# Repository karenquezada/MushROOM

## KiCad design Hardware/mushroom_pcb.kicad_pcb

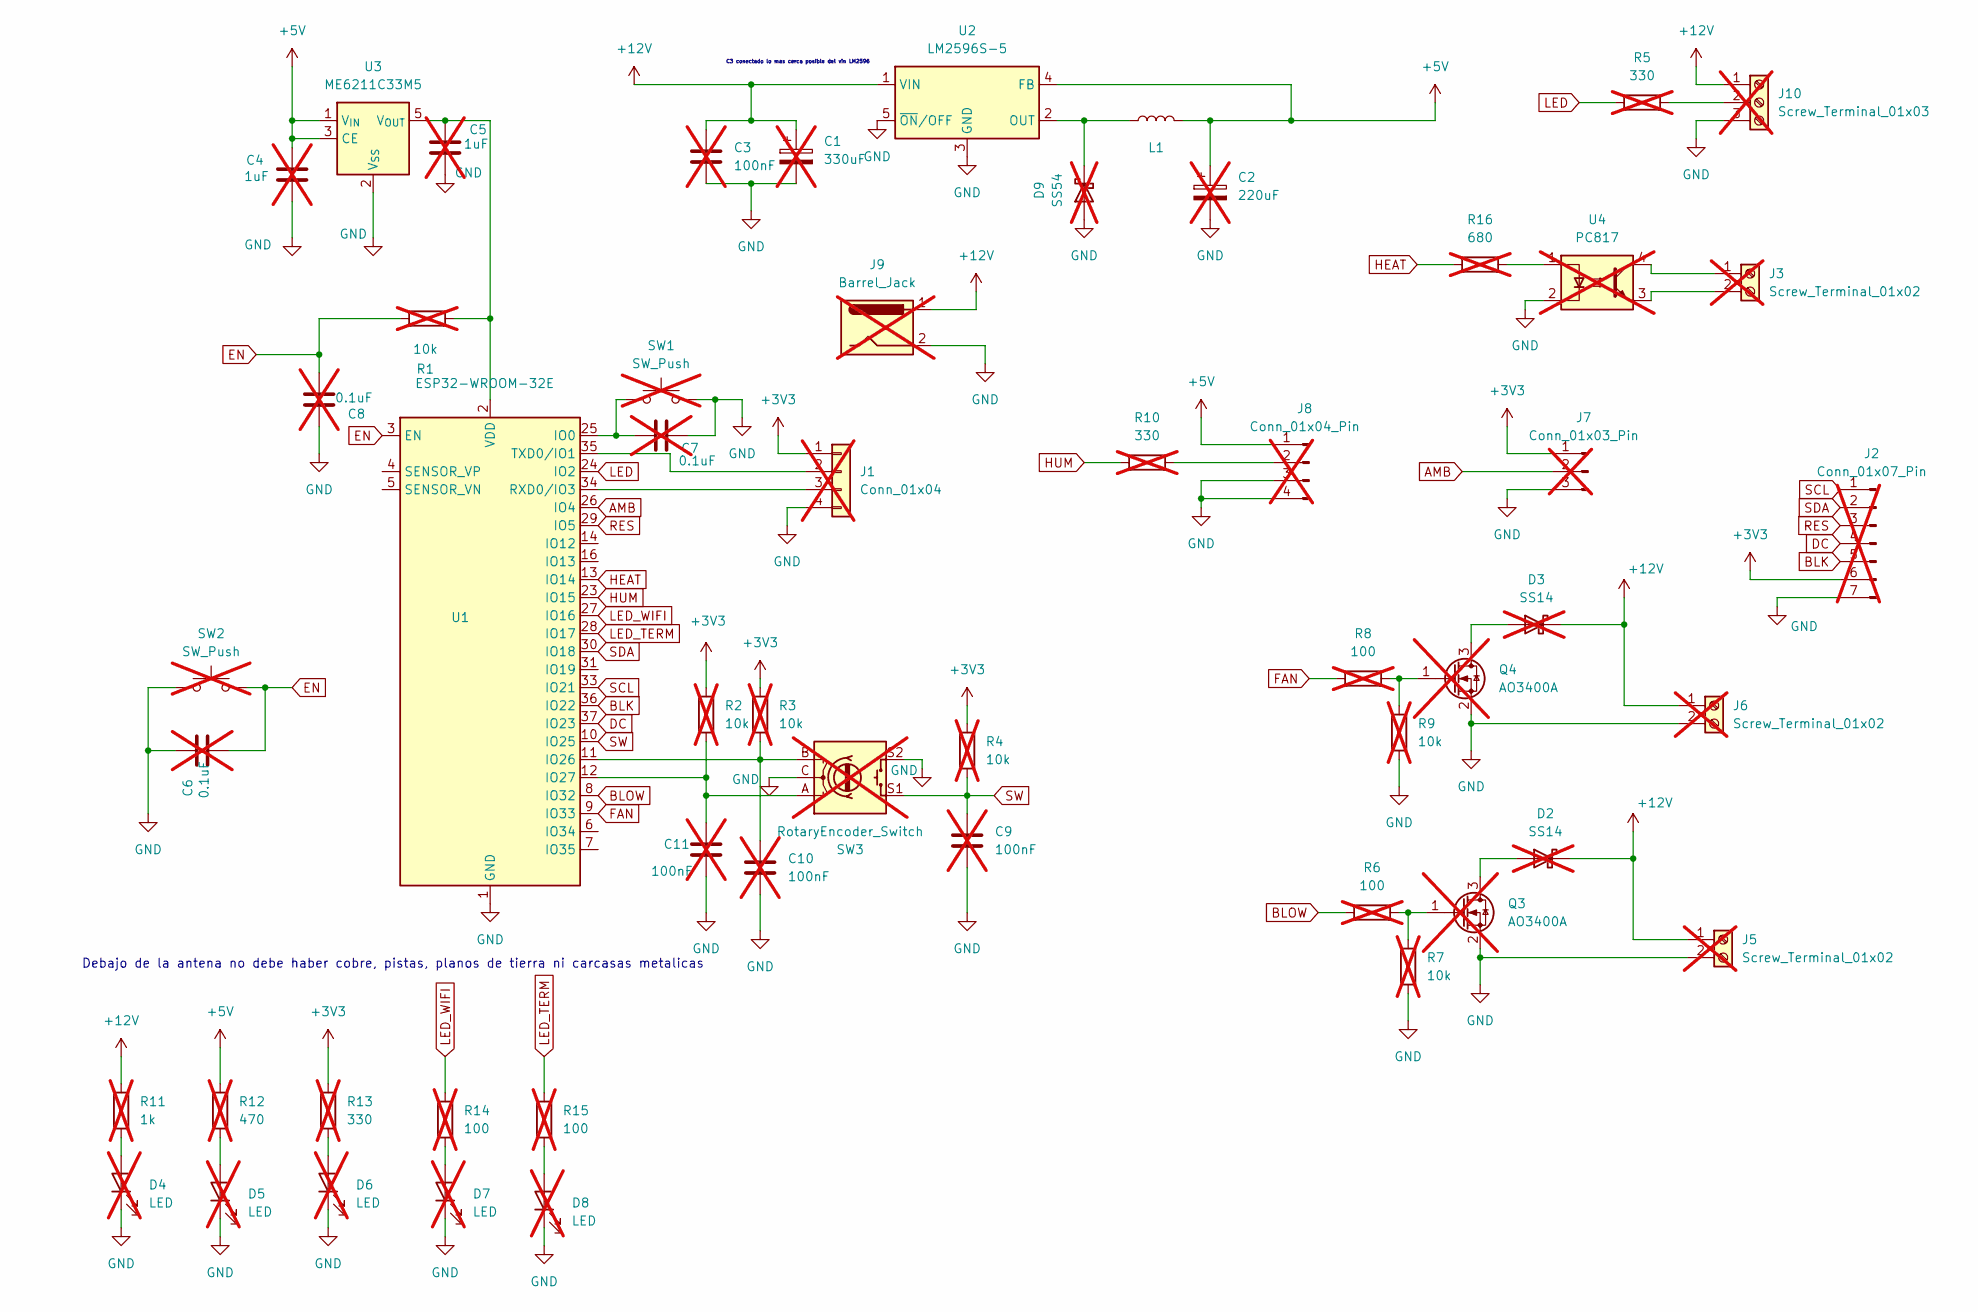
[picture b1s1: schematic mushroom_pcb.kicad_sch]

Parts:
C1: 330uF; CP_Elec_8x10.5; not fitted
C2: 220uF; CP_Elec_8x10.5; not fitted
C3, C9, C10, C11: 100nF; C_0805_2012Metric; not fitted
C4, C5: 1uF; C_0805_2012Metric; not fitted
C6, C7, C8: 0.1uF; C_0805_2012Metric; not fitted
D2, D3: SS14; D_SMA; not fitted
D4, D5, D6, D7, D8: LED; LED_0805_2012Metric; not fitted
D9: SS54; D_SMA; not fitted
J1: Conn_01x04; PinHeader_1x04_P2.54mm_Vertical; not fitted
J2: Conn_01x07_Pin; JST_XH_B7B-XH-A_1x07_P2.50mm_Vertical; not fitted
J3, J5, J6: Screw_Terminal_01x02; TerminalBlock_Phoenix_PT-1,5-2-5.0-H_1x02_P5.00mm_Horizontal; not fitted
J7: Conn_01x03_Pin; JST_XH_S3B-XH-A_1x03_P2.50mm_Horizontal; not fitted
J8: Conn_01x04_Pin; JST_XH_S4B-XH-A_1x04_P2.50mm_Horizontal; not fitted
J9: Barrel_Jack; BarrelJack_CUI_PJ-102AH_Horizontal; not fitted
J10: Screw_Terminal_01x03; TerminalBlock_Phoenix_PT-1,5-3-5.0-H_1x03_P5.00mm_Horizontal; not fitted
L1: 33uH; L_12x12mm_H8mm
Q3, Q4: AO3400A; SOT-23; not fitted
R1, R2, R3, R4, R7, R9: 10k; R_0805_2012Metric_Pad1.20x1.40mm_HandSolder; not fitted
R5, R10, R13: 330; R_0805_2012Metric_Pad1.20x1.40mm_HandSolder; not fitted
R6, R8, R14, R15: 100; R_0805_2012Metric_Pad1.20x1.40mm_HandSolder; not fitted
R11: 1k; R_0805_2012Metric_Pad1.20x1.40mm_HandSolder; not fitted
R12: 470; R_0805_2012Metric_Pad1.20x1.40mm_HandSolder; not fitted
R16: 680; R_0805_2012Metric_Pad1.20x1.40mm_HandSolder; not fitted
SW1, SW2: SW_Push; SW_Push_1P1T_XKB_TS-1187A; not fitted
SW3: RotaryEncoder_Switch; RotaryEncoder_Alps_EC11E-Switch_Vertical_H20mm; not fitted
U1: ESP32-WROOM-32E; ESP32-WROOM-32D
U2: LM2596S-5; TO-263-5_TabPin3
U3: ME6211C33M5; SOT-23-5
U4: PC817; DIP-4_W7.62mm; not fitted

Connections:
+3V3: J1.1, J2.6, J7.1, R2.1, R3.1, R4.1, R13.1
+5V: C2.1, C4.1, J8.1, L1.2, R12.1, U2.4 (FB), U3.1 (V_{IN}), U3.3 (CE)
+12V: C1.1, C3.1, D2.1 (K), D3.1 (K), J5.1, J6.1, J9.1, J10.1, R11.1, U2.1 (VIN)
AMB: J7.2, U1.26 (IO4)
BLK: J2.5, U1.36 (IO22)
BLOW: R6.1, U1.8 (IO32)
DC: J2.4, U1.37 (IO23)
EN: C6.2, C8.2, R1.2, SW2.2, U1.3 (EN)
FAN: R8.1, U1.9 (IO33)
GND: C1.2, C2.2, C3.2, C4.2, C5.2, C6.1, C7.2, C8.1, C9.2, C10.2, C11.2, D4.1 (K), D5.1 (K), D6.1 (K), D7.1 (K), D8.1 (K), D9.2 (A), J1.4, J2.7, J5.2, J6.2, J7.3, J8.3, J8.4, J9.2, J10.3, Q3.2 (S), Q4.2 (S), R7.2, R9.2, SW1.2, SW2.1, SW3.C, SW3.S2, U1.1 (GND), U1.15 (GND), U1.38 (GND), U1.39 (GND), U2.3 (GND), U2.5 (~ON/OFF), U3.2 (V_{SS}), U4.2
HEAT: R16.1, U1.13 (IO14)
HUM: R10.1, U1.23 (IO15)
LED: R5.1, U1.24 (IO2)
LED_TERM: R15.1, U1.28 (IO17)
LED_WIFI: R14.1, U1.27 (IO16)
unnamed: D2.2 (A), Q3.3 (D)
unnamed: D3.2 (A), Q4.3 (D)
unnamed: D4.2 (A), R11.2
unnamed: D5.2 (A), R12.2
unnamed: D6.2 (A), R13.2
unnamed: D7.2 (A), R14.2
unnamed: D8.2 (A), R15.2
unnamed: D9.1 (K), L1.1, U2.2 (OUT)
unnamed: J1.2, U1.35 (TXD0/IO1)
unnamed: J1.3, U1.34 (RXD0/IO3)
unnamed: J3.1, U4.4
unnamed: J3.2, U4.3
unnamed: J8.2, R10.2
unnamed: J10.2, R5.2
unnamed: Q3.1 (G), R6.2, R7.1
unnamed: Q4.1 (G), R8.2, R9.1
unnamed: R16.2, U4.1
unnamed: C7.1, SW1.1, U1.25 (IO0)
unnamed: C10.1, R3.2, SW3.B, U1.11 (IO26)
unnamed: C11.1, R2.2, SW3.A, U1.12 (IO27)
unnamed: C5.1, R1.1, U1.2 (VDD), U3.5 (V_{OUT})
RES: J2.3, U1.29 (IO5)
SCL: J2.1, U1.33 (IO21)
SDA: J2.2, U1.30 (IO18)
SW: C9.1, R4.2, SW3.S1, U1.10 (IO25)

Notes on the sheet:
Debajo de la antena no debe haber cobre, pistas, planos de tierra ni carcasas metalicas
C3 conectado lo mas cerca posible del vin LM2596

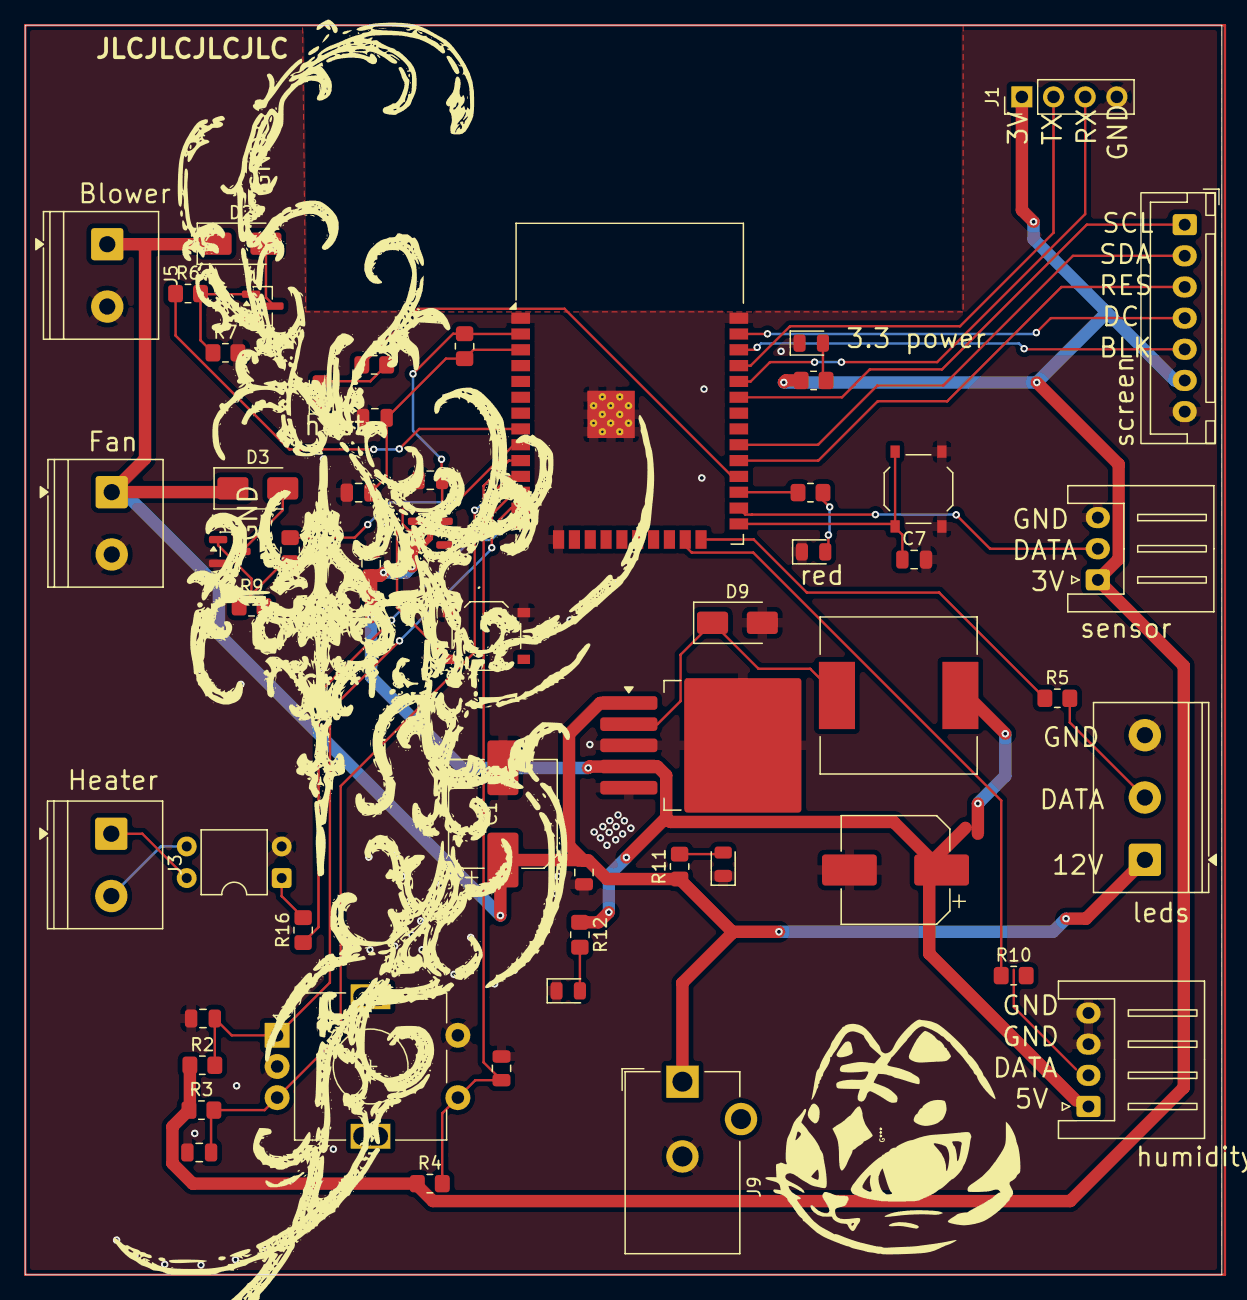
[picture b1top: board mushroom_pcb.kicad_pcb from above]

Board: 2 copper layers, 96.0 x 100.2 mm, 54 parts (0 on the bottom side), 40 nets.

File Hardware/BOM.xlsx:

330uF | C1 | CP_Elec_8x10.5
100nF | C10 | C_0805_2012Metric
100nF | C11 | C_0805_2012Metric
220uF | C2 | CP_Elec_8x10.5
100nF | C3 | C_0805_2012Metric
1uF | C4 | C_0805_2012Metric
1uF | C5 | C_0805_2012Metric
0.1uF | C6 | C_0805_2012Metric
0.1uF | C7 | C_0805_2012Metric
0.1uF | C8 | C_0805_2012Metric
100nF | C9 | C_0805_2012Metric
PMEG040V050EPD | D1 | Nexperia_CFP15_SOT-1289
SS14 | D2,D3 | D_SMA
LED | D4 | LED_0805_2012Metric
LED | D5 | LED_0805_2012Metric
LED | D6 | LED_0805_2012Metric
LED | D7 | LED_0805_2012Metric
LED | D8 | LED_0805_2012Metric
Conn_01x04 | J1 | PinHeader_1x04_P2.54mm_Vertical
Screw_Terminal_01x03 | J10 | TerminalBlock_Phoenix_PT-1,5-3-5.0-H_1x03_P5.00mm_Horizontal
Conn_01x07_Pin | J2 | JST_XH_B7B-XH-A_1x07_P2.50mm_Vertical
Screw_Terminal_01x02 | J3 | TerminalBlock_Phoenix_PT-1,5-2-5.0-H_1x02_P5.00mm_Horizontal
Screw_Terminal_01x02 | J5 | TerminalBlock_Phoenix_PT-1,5-2-5.0-H_1x02_P5.00mm_Horizontal
Screw_Terminal_01x02 | J6 | TerminalBlock_Phoenix_PT-1,5-2-5.0-H_1x02_P5.00mm_Horizontal
Conn_01x03_Pin | J7 | JST_XH_S3B-XH-A_1x03_P2.50mm_Horizontal
Conn_01x04_Pin | J8 | JST_XH_S4B-XH-A_1x04_P2.50mm_Horizontal
Barrel_Jack | J9 | BarrelJack_SwitchcraftConxall_RAPC10U_Horizontal
33uH | L1 | L_12x12mm_H8mm
AO3400A | Q3,Q4 | SOT-23
10k | R1 | R_0805_2012Metric_Pad1.20x1.40mm_HandSolder
330 | R10 | R_0805_2012Metric_Pad1.20x1.40mm_HandSolder
1k | R11 | R_0805_2012Metric_Pad1.20x1.40mm_HandSolder
470 | R12 | R_0805_2012Metric_Pad1.20x1.40mm_HandSolder
330 | R13 | R_0805_2012Metric_Pad1.20x1.40mm_HandSolder
100 | R14 | R_0805_2012Metric_Pad1.20x1.40mm_HandSolder
100 | R15 | R_0805_2012Metric_Pad1.20x1.40mm_HandSolder
680 | R16 | R_0805_2012Metric_Pad1.20x1.40mm_HandSolder
10k | R2 | R_0805_2012Metric_Pad1.20x1.40mm_HandSolder
10k | R3 | R_0805_2012Metric_Pad1.20x1.40mm_HandSolder
10k | R4 | R_0805_2012Metric_Pad1.20x1.40mm_HandSolder
330 | R5 | R_0805_2012Metric_Pad1.20x1.40mm_HandSolder
100 | R6 | R_0805_2012Metric_Pad1.20x1.40mm_HandSolder
10k | R7 | R_0805_2012Metric_Pad1.20x1.40mm_HandSolder
100 | R8 | R_0805_2012Metric_Pad1.20x1.40mm_HandSolder
10k | R9 | R_0805_2012Metric_Pad1.20x1.40mm_HandSolder
SW_Push | SW1,SW2 | SW_Push_1P1T_XKB_TS-1187A
RotaryEncoder_Switch | SW3 | RotaryEncoder_Alps_EC11E-Switch_Vertical_H20mm
ESP32-WROOM-32E | U1 | ESP32-WROOM-32D
LM2596S-5 | U2 | TO-263-5_TabPin3
ME6211C33M5 | U3 | SOT-23-5
PC817 | U4 | DIP-4_W7.62mm

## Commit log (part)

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2025-08-11 algunos borradores + telegrambot
2025-09-25 probar blower y mejorar los datos del sensor
2025-10-05 task dht22 + screen funcionales, incorporacion main exitosa
2025-10-22 codigo de humidificacion
